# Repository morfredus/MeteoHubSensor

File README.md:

# MeteoHubSensor

> 🇫🇷 Version française : [README.fr.md](README.fr.md)

Standalone outdoor weather probe, linked over **ESP-NOW** to the **MeteoHub** station. Target board: **ESP32-S3 Super Mini** (RGB LED, no screen).

---

## 1. Responsibility

**MeteoHubSensor** has a single responsibility: **measure the outdoor environment and transmit its raw metrics over ESP-NOW**.

This node is **not a new morfSystem component**. No web server, no local history.

### Roles:
- **Super Mini (Outdoor)**: *"I measure, I blink the status, I transmit."*
- **MeteoHub**: *"I receive, validate, store, display and expose."*

---

## 2. ESP-NOW architecture

```
              ┌─────────────────┐
              │  ESP32-S3       │
              │  MeteoHub       │
              └────────┬────────┘
                       │ ESP-NOW
              ┌────────▼────────┐
              │  Super Mini     │
              │  RGB LED        │
              │  AHT20 / BMP280 │
              └────────┬────────┘
                       │
              ┌────────┴────────┐
              ▼                 ▼
         Temperature        Humidity
```

### Changing hub: pairing with a long press on BOOT

The probe talks to **a single** MeteoHub, in unicast. That hub's MAC is stored in
the probe's NVS: there is no need to know it at build time, nor to reflash to
change hub.

1. Leave **only** the MeteoHub to pair powered on within radio range
   (MeteoHub **≥ 1.46.0**).
2. With the probe running, hold **BOOT for about 3 s**, until the LED turns
   **solid blue**, then **release**: pairing starts on release. A press longer
   than 10 s is ignored (button considered stuck). Do not hold BOOT while
   plugging the probe in: that is the ESP32 flashing mode.
3. The probe sweeps channels 1 to 13 asking "who is a hub?". The hub answers with
   its identity and MAC; the probe confirms in unicast and waits for the hub's
   acknowledgement.
4. **3 green flashes**: paired, the new MAC is in NVS and measurements go to this
   hub in unicast. **3 red flashes**: failure, the previous association is **kept
   as it was**.

Rules:

- **Deliberate only.** A hub that is off or out of range never triggers a change
  of receiver: the probe keeps its measurements pending and keeps aiming at its
  hub.
- **A failure erases nothing.** Until a new hub has answered AND acknowledged the
  confirmation, the probe keeps the old MAC (in NVS and in memory).
- **Several hubs in range.** If two different hubs answer during the sweep, the
  probe refuses (red flashes) rather than pick one at random. Once paired, the
  other hubs can be switched back on: the probe finds ITS hub's channel through
  the exact BSSID of its "MH-NOW" access point, no longer through the first
  "MH-NOW" it sees.
- **No duplicate, no gap.** The confirmation carries the last measurement number
  acknowledged by the old hub: the new hub resumes from there and only receives
  the measurements still pending.
- **Stuck button = no effect.** A permanent press (an enclosure pressing the
  button, moisture on GPIO0) is never released: it starts no pairing, and the
  button wake-up is not even armed while GPIO0 stays low. Measurements carry on
  normally.
- Search bounded to **60 s**. A short press is ignored.
- The hub (≥ 1.47.0) **only archives the probe that chose it**: a bench probe
  powered on next to it can no longer mix its readings with the outdoor ones. The
  press wakes the probe from sleep; it then goes back to sleep for the remaining
  time, without shifting the measurement cadence.

Without a stored pairing (new probe, erased flash), the probe **sends nothing**:
`ESPNOW_RECEIVER_MAC` (`include/config.h`) is zero since 0.25.0. It keeps its
measurements pending and no longer scans channels until a long press on BOOT has
paired it. A hard-coded MAC would have targeted one specific hub, and after
swapping hubs (production ↔ test bench) an erased probe would have sent its
readings to the wrong hub.

### Local buffer: no measurement lost, without draining the battery

Each measurement is written to flash **before** it is sent, then kept until the
hub acknowledges it. If the hub is off or out of range, the probe later resends
what is missing, in order, at most 10 measurements per wake-up. Retention: 30
days of pending measurements.

Since 0.24.0 this buffer is a **segmented journal**: one small file per day of
measurements (`/mhs/<seq>.seg`), written by appending only. The acknowledgement
watermark lives in NVS, and a fully acknowledged segment is deleted. The former
buffer, a single 276 KB file, was copied in full by LittleFS at every
measurement: 4.5 s measured, radio on. On the first boot in 0.24.0, the
measurements still pending in the old file are taken over, then it is erased.

---

## 3. Hardware

The pinout lives in `include/board_config.h`, selected by the `SENSOR_BOARD_S3`
define set by the PlatformIO environment.

**ESP32-S3 Super Mini** (env `sonde-supermini`)
- 4 MB flash + 2 MB quad PSRAM (unused), native USB CDC. **No screen** (status on the LED).
- Status = RGB LED on GPIO 48 (blue acquisition, green OK, red error).
- **I2C**: SDA = GP8, SCL = GP9. Battery: Li-ion, 3.3 V regulator module, 100k/100k divider on GP4.
- ESP-NOW capped at **11 dBm** (hardware constraint confirmed by testing: full power = no ACK).
- **Sensors**: DHT22 on GP1 (reference for temperature and humidity, no fallback), BMP280 (pressure only; the AHT20 of the module is no longer read). Anemometer reserve on GP5.
- Details (French): [`docs/cablage.md`](docs/cablage.md).

---

## 4. RGB LED

- **Blue**: boot and acquisition.
- **Green**: delivery confirmed (the hub acknowledged, unicast ACK).
- **Red**: not delivered (no ACK from the hub).
- **Solid blue** (after ~3 s holding BOOT): pairing in progress.
- **3 green / red flashes**: pairing succeeded / failed (association unchanged).

---

## 5. Build and flash

1. Copy `include/secrets_example.h` to `include/secrets.h` **in this project**.

```bash
# ESP32-S3 Super Mini
pio run -e sonde-supermini
pio run -e sonde-supermini -t upload
pio run -e sonde-supermini -t monitor
```

If the serial port does not show up: hold BOOT, tap RESET, release BOOT.

---

## 6. Author & License

Developed by **morfredus** for the **MeteoHub** weather station.
License: **GPL v3**.

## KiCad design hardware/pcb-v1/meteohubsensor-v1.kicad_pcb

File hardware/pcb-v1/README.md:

# Carte v1 de MeteoHubSensor (projet KiCad 10)

Platine dessinée pour remplacer la v1 montée sur platine à bandes (uPesy) : même schéma, mais gravée,
avec l'ESP32-S3 Super Mini sur supports pour pouvoir l'échanger sans dessoudage.

Ouvrir `meteohubsensor-v1.kicad_pro` avec KiCad 10.0.x. Fichiers : schéma, PCB routé (66 x 50 mm, deux
couches, plan de masse GND sur les deux faces), bibliothèque `morfsensor` (symboles et empreintes propres au projet).

## Ce que porte la carte

| Réf. | Rôle | Reliée à |
| :--- | :--- | :--- |
| U1 | ESP32-S3 Super Mini N4R2 sur 2 supports femelles 1x9 | voir ci-dessous |
| U2 | Module abaisseur 3,3 V (Youmi, SOT-223) | VIN = + accu, VOUT = rail 3V3 |
| J1 | Accu (JST-XH 2 broches : + / -) | VBAT, GND |
| J2 | BMP280 (JST-XH 4 broches : 3V3, SCL, SDA, GND) | GP9 (SCL), GP8 (SDA) |
| J3 | DHT22 (JST-XH 3 broches : 3V3, DATA, GND) | GP1 |
| J4 | Anémomètre, futur (3V3, IMPULSION, GND) | GP5 |
| J5 | Pluviomètre, futur (3V3, IMPULSION, GND) | GP7 |
| J6 | Girouette, future (3V3, ADC, GND) | GP2 |
| R1, R2 | Pont 100 kohm / 100 kohm sur le + accu, avant le régulateur | milieu = GP4 |
| C3 | 100 nF sur le noeud du pont (stabilise la lecture ADC) | GP4 / GND |
| C1, C2 | 100 nF céramique + 220 uF électrolytique, collés aux broches 3V3/GND du S3 | rail 3V3 |
| R3 | 10 kohm de rappel du DHT22 (omettre avec un module 3 broches qui l'embarque) | DATA / 3V3 |
| H1 à H4 | Trous de fixation M3 | |

Le régulateur alimente la broche **3V3** du S3 (pas la 5V), comme sur la v1 actuelle. Broches du S3 laissées
libres : TX, RX, GP3, GP6, 5V, GP10 à GP13.

## Masse et modèles 3D

La masse (GND) est un plan de cuivre sur les deux faces : toutes les broches GND des connecteurs et des
composants s'y raccordent par leurs pastilles traversantes, sans piste dédiée. Seules l'alimentation et les signaux
sont tracés. Des pistes GND explicites ont été
essayées puis retirées : elles alourdissaient le dessin sans rien apporter, le plan relie déjà tout.
Les empreintes `ESP32-S3_SuperMini_Socket` et `Regulator_Module_3V3` embarquent un modèle 3D simplifié
(`morfsensor.3dshapes/`) : supports et module avec USB-C et antenne, platine du régulateur avec SOT-223.

## Brochage des connecteurs JST-XH

Broche 1 à gauche (côté de l'ergot carré de l'embase), vue de dessus, détrompeur vers le bas.

| Connecteur | Broche 1 | Broche 2 | Broche 3 | Broche 4 | Référence suivie |
| :--- | :--- | :--- | :--- | :--- | :--- |
| J1 accu | + accu | - accu | | | rouge (+) puis noir (-), usage courant des accus Li-ion |
| J2 BMP280 | 3V3 | SCL | SDA | GND | + puis signaux puis GND, comme les autres ; SCL et SDA se relient sans croisement |
| J3 DHT22 | 3V3 | DATA | GND | | ordre de la fiche technique du DHT22 / AM2302 (VDD, DATA, GND) |
| J4 anémomètre | 3V3 | IMPULSION | GND | | même ordre que J3 |
| J5 pluviomètre | 3V3 | IMPULSION | GND | | même ordre que J3 |
| J6 girouette | 3V3 | ADC | GND | | même ordre que J3 |

Les modules BMP280 courants sont étiquetés dans un autre ordre (VCC, GND, SCL, SDA) : les câbles se sertissent à
l'ordre du connecteur de la carte, pas à celui du module.

## Orientation du module régulateur

Vue de dessus, broches vers le bas (soudées sur la carte), IN à gauche et OUT à droite : sur chaque paire,
VIN (gauche) et VOUT (droite) sont sur la broche du bas, GND sur la broche du haut.

## Repères des broches du S3

Les numéros de pastilles de U1 sont les repères imprimés sur le module, vue de dessus, USB en haut : à
gauche de haut en bas TX, RX, 1, 2, 3, 4, 5, 6, 7 ; à droite de haut en bas 5V, GND, 3V3, 13, 12, 11, 10, 9, 8.
Pastille 8 = GPIO8 = SDA, pastille 9 = GPIO9 = SCL, et ainsi de suite : aucune table de correspondance à tenir.
J6 (girouette) ne porte que le signal brut sur GP2 : le pont diviseur propre à la girouette reste à définir
avec le firmware.

## Antenne

Le S3 est implanté **USB vers l'intérieur** : l'antenne céramique se retrouve au **bord bas** de la carte.
Une zone d'exclusion (cuivre, pistes, vias, plan de masse, sur les deux faces) couvre l'espace sous l'antenne
et jusqu'au bord. Aucune piste n'approche l'antenne : les signaux des deux rangées partent vers l'extérieur.

Limite connue : l'USB du module est tourné vers l'intérieur de la carte. Pour flasher, enlever le module de
ses supports (c'est l'intérêt de la prise).

## Cotes relevées sur les modules

- **ESP32-S3 Super Mini** : 15,9 mm hors tout entre les deux rangées de broches, soit 15,24 mm entre axes (broche de
  0,64 mm), pas de 2,54 mm comme sur une platine d'essai. Empreinte `ESP32-S3_SuperMini_Socket`.
- **Module régulateur** : circuit de 25,6 x 11,3 mm. Broches standard (0,64 mm) sur la grille de 2,54 mm, comme les
  deux modules qui entrent dans une platine d'essai : deux paires espacées de 22,86 mm entre axes (9 pas) dans la
  longueur, pas de 2,54 mm dans chaque paire (3 mm hors tout dans la largeur). Empreinte `Regulator_Module_3V3`.
  La position des paires dans la largeur du circuit est supposée centrée : elle ne change que le contour dessiné,
  pas le perçage.

## À vérifier avant fabrication

1. **Module régulateur** : vérifier que son orientation réelle (IN à gauche, VIN sur la broche du bas) correspond à
   l'empreinte, en le posant sur la carte imprimée ou sur un gabarit.
2. **Connecteurs** : les câbles existants ne suivent pas forcément cet ordre ; les recréer au brochage du tableau.

Rappel du point de vigilance de `docs/cablage.md` : la plage d'entrée annoncée du module (4,5 à 7 V) est
au-dessus de celle d'un accu Li-ion. À mesurer sur banc avant de figer la carte.

## Contrôles passés (KiCad 10.0.7, `kicad-cli`)

- ERC : 0 violation.
- DRC avec parité schéma/PCB : 0 erreur, 0 piste non connectée. Restent des avertissements de sérigraphie
  (textes proches des contours de connecteurs).

Les fichiers ont été générés par script puis vérifiés par ces commandes ; les ouvrir une fois dans KiCad et
lancer `Fichier > Enregistrer` les remet au format exact de l'éditeur.

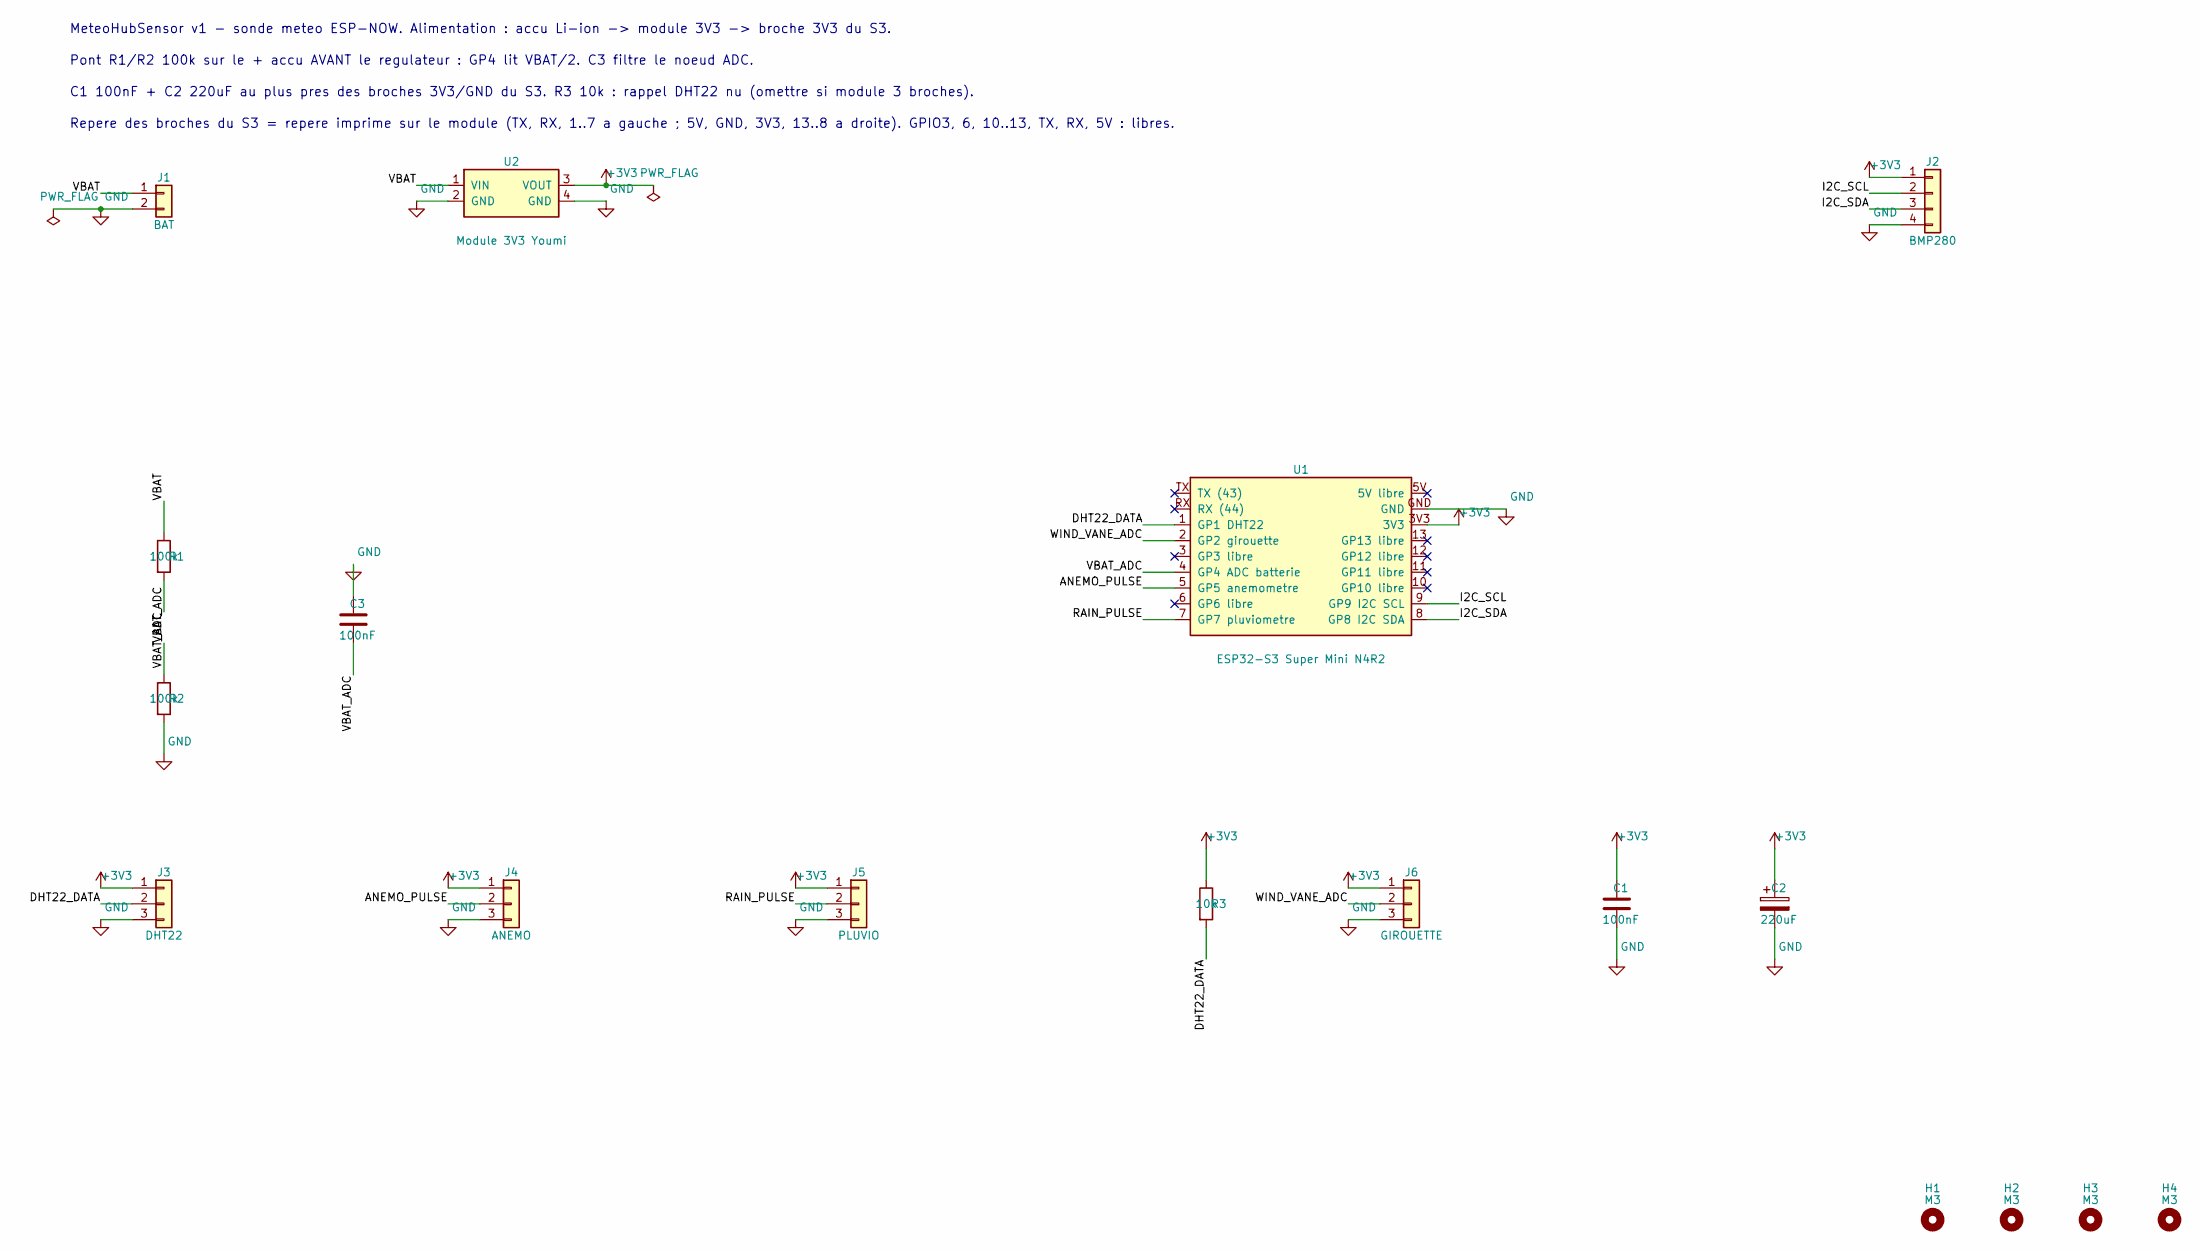
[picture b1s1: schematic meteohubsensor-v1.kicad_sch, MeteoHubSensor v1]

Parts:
C1, C3: 100nF; C_Disc_D3.0mm_W2.0mm_P2.50mm
C2: 220uF; CP_Radial_D6.3mm_P2.50mm
H1, H2, H3, H4: M3; MountingHole_3.2mm_M3
J1: BAT; JST_XH_B2B-XH-A_1x02_P2.50mm_Vertical
J2: BMP280; JST_XH_B4B-XH-A_1x04_P2.50mm_Vertical
J3: DHT22; JST_XH_B3B-XH-A_1x03_P2.50mm_Vertical
J4: ANEMO; JST_XH_B3B-XH-A_1x03_P2.50mm_Vertical
J5: PLUVIO; JST_XH_B3B-XH-A_1x03_P2.50mm_Vertical
J6: GIROUETTE; JST_XH_B3B-XH-A_1x03_P2.50mm_Vertical
R1, R2: 100k; R_Axial_DIN0207_L6.3mm_D2.5mm_P2.54mm_Vertical
R3: 10k; R_Axial_DIN0207_L6.3mm_D2.5mm_P2.54mm_Vertical
U1: ESP32-S3 Super Mini N4R2; ESP32-S3_SuperMini_Socket
U2: Module 3V3 Youmi; Regulator_Module_3V3

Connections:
+3V3: C1.1, C2.1, J2.1, J3.1, J4.1, J5.1, J6.1, R3.1, U1.3V3, U2.3 (VOUT)
/ANEMO_PULSE: J4.2, U1.5 (GP5 anemometre)
/DHT22_DATA: J3.2, R3.2, U1.1 (GP1 DHT22)
/I2C_SCL: J2.2, U1.9 (GP9 I2C SCL)
/I2C_SDA: J2.3, U1.8 (GP8 I2C SDA)
/RAIN_PULSE: J5.2, U1.7 (GP7 pluviometre)
/VBAT: J1.1, R1.1, U2.1 (VIN)
/VBAT_ADC: C3.2, R1.2, R2.1, U1.4 (GP4 ADC batterie)
/WIND_VANE_ADC: J6.2, U1.2 (GP2 girouette)
GND: C1.2, C2.2, C3.1, J1.2, J2.4, J3.3, J4.3, J5.3, J6.3, R2.2, U1.GND, U2.2 (GND), U2.4 (GND)

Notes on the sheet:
MeteoHubSensor v1 - sonde meteo ESP-NOW. Alimentation : accu Li-ion -> module 3V3 -> broche 3V3 du S3.
Pont R1/R2 100k sur le + accu AVANT le regulateur : GP4 lit VBAT/2. C3 filtre le noeud ADC.
C1 100nF + C2 220uF au plus pres des broches 3V3/GND du S3. R3 10k : rappel DHT22 nu (omettre si module 3 broches).
Repere des broches du S3 = repere imprime sur le module (TX, RX, 1..7 a gauche ; 5V, GND, 3V3, 13..8 a droite). GPIO3, 6, 10..13, TX, RX, 5V : libres.

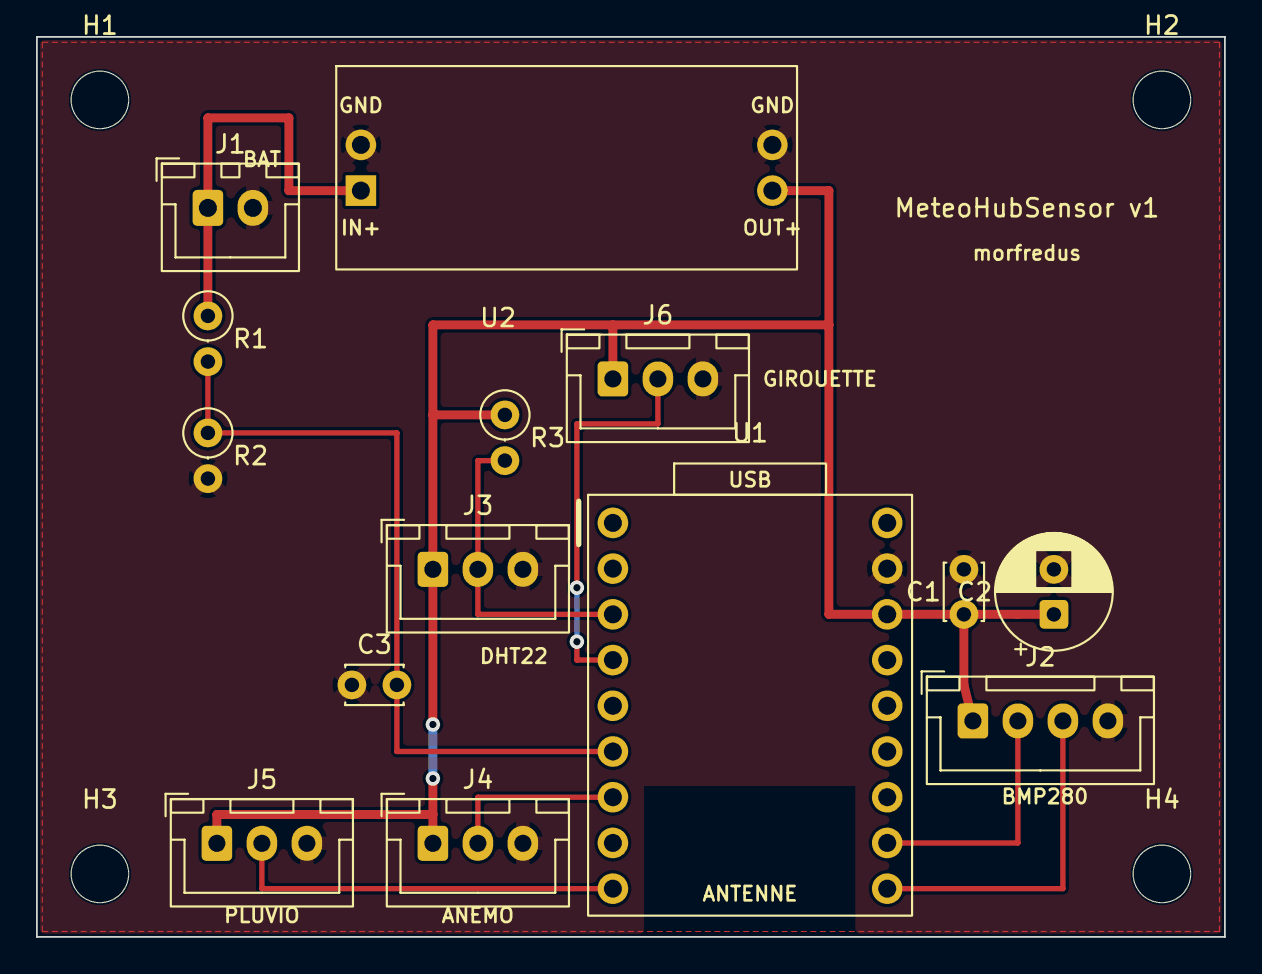
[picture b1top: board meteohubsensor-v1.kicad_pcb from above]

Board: 2 copper layers, 66.0 x 50.0 mm, 18 parts (0 on the bottom side), 10 nets.

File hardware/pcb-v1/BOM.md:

# Liste des composants - carte v1 de MeteoHubSensor

Liste tirée du schéma (`meteohubsensor-v1.kicad_sch`). Toutes les pièces de la carte sont traversantes : aucune
soudure CMS, **52 pastilles à souder** au total. Aucune référence de fournisseur (LCSC, Mouser...) n'est donnée :
elles n'ont pas été vérifiées.

## 1. Soudé sur la carte

### Résistances (3)

| Réf. | Qté | Valeur | Détail | Rôle |
| :--- | :-: | :--- | :--- | :--- |
| R1, R2 | 2 | 100 kohm | Axiale 1/4 W, tolérance **1 %** conseillée, boîtier DIN0207 | Pont de mesure de l'accu (GP4) |
| R3 | 1 | 10 kohm | Axiale 1/4 W, boîtier DIN0207 | Rappel du DHT22 (omettre avec un module 3 broches qui l'embarque) |

### Condensateurs (3)

| Réf. | Qté | Valeur | Détail | Rôle |
| :--- | :-: | :--- | :--- | :--- |
| C1 | 1 | 100 nF | Céramique disque, 50 V, pas 2,5 mm | Découplage près des broches 3V3/GND du S3 |
| C3 | 1 | 100 nF | Céramique disque, 50 V, pas 2,5 mm | Filtre du noeud ADC (GP4) |
| C2 | 1 | 220 uF | Électrolytique radial, **10 V ou plus**, diamètre 6,3 mm, pas 2,5 mm | Réserve de courant pour les pointes d'émission |

### Embases JST-XH (6 embases, 18 broches), pas 2,50 mm, verticales

| Réf. | Nom | Broches | Référence JST | Brochage (1 à n) |
| :--- | :--- | :-: | :--- | :--- |
| J1 | BAT | 2 | B2B-XH-A | + accu, - accu |
| J2 | BMP280 | 4 | B4B-XH-A | 3V3, SCL, SDA, GND |
| J3 | DHT22 | 3 | B3B-XH-A | 3V3, DATA, GND |
| J4 | ANEMO | 3 | B3B-XH-A | 3V3, impulsion, GND |
| J5 | PLUVIO | 3 | B3B-XH-A | 3V3, impulsion, GND |
| J6 | GIROUETTE | 3 | B3B-XH-A | 3V3, ADC, GND |

Récapitulatif : 1 x 2 broches, 4 x 3 broches (12 broches), 1 x 4 broches, soit 2 + 12 + 4 = 18 broches.

### Supports et module

| Réf. | Qté | Pièce | Détail |
| :--- | :-: | :--- | :--- |
| U1 | 2 | Barrette femelle 1x9, pas 2,54 mm | Une par rangée du S3 (18 broches au total), entraxe des rangées 15,24 mm |
| U2 | 1 | Module abaisseur 3,3 V (Youmi, SOT-223) | 4 broches mâles soudées : deux paires espacées de 22,86 mm, circuit 25,6 x 11,3 mm |

Trous de fixation H1 à H4 : 4 trous M3 (3,2 mm), aucune pièce sur la carte.

## 2. À fournir, non soudé sur la carte

| Qté | Pièce | Remarque |
| :-: | :--- | :--- |
| 1 | ESP32-S3 Super Mini N4R2 | Se pose sur les supports U1, USB-C vers l'intérieur de la carte |
| 1 | Module BMP280 (avec ou sans AHT20) | Seule la pression est lue |
| 1 | DHT22 (ou module 3 broches) | Température et humidité de référence |
| 1 | Accu Li-ion 3,7 V | 3000 mAh en place ; chargé hors de la sonde, sans protection sur cette carte |
| 1 | Anémomètre, 1 pluviomètre, 1 girouette | Futurs ; seuls les connecteurs J4, J5, J6 sont prévus |
| 1 | Boîtier femelle JST-XHP 2 broches | Pour J1 |
| 4 | Boîtiers femelles JST-XHP 3 broches | Pour J3, J4, J5, J6 |
| 1 | Boîtier femelle JST-XHP 4 broches | Pour J2 |
| 18 | Cosses à sertir JST-XH (SXH) | 2 + 12 + 4, prévoir quelques cosses de plus pour les ratés de sertissage |
| - | Fil souple 22 à 26 AWG | Pour les câbles des capteurs et de l'accu |
| 4 | Vis M3 et entretoises | Pour la fixation, si le boîtier en demande |

## 3. Totaux

| Famille | Pièces | Pastilles à souder |
| :--- | :-: | :-: |
| Résistances | 3 | 6 |
| Condensateurs | 3 | 6 |
| Embases JST-XH | 6 | 18 |
| Barrettes femelles 1x9 | 2 | 18 |
| Module régulateur | 1 | 4 |
| **Total** | **15** | **52** |

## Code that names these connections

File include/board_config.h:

#pragma once
#include <Arduino.h>

// ============================================================================
// Brochage MeteoHubSensor - ESP32-S3 Super Mini
// ============================================================================
// Cible unique (env sonde-supermini, define SENSOR_BOARD_S3). Le reste du firmware ne
// connait que les alias PIN_* et le drapeau SENSOR_NEEDS_TX_LIMIT : ajouter une
// autre carte se ferait ici, sans toucher aux modules. (La cible C3 HW-675 a ete
// retiree, et avec elle le module d'ecran OLED qui ne servait qu'a elle.)
// ============================================================================

// ---------------------------------------------------------------------------
// ESP32-S3 Super Mini (LED RGB seule, sans ecran)
// ---------------------------------------------------------------------------
// USB natif : GPIO 19/20. BOOT : GPIO 0 (non sorti). Straps : 45/46.
// LED RGB onboard : GPIO 48 (GPIO 46 = input-only, ignore malgre le pinout).
constexpr char BOARD_NAME[] = "ESP32-S3 Super Mini";

// --- Module BMP280 (0x77) + AHT20 (0x38) : seule la pression du BMP280 est utilisee ---
// Cablage : fil SDA du module -> GP8, fil SCL du module -> GP9, 3V3, GND.
constexpr uint8_t PIN_SENSOR_SDA = 8;
constexpr uint8_t PIN_SENSOR_SCL = 9;
constexpr int8_t PIN_SENSOR_POWER = -1; // -1 = alim 3V3 permanente

// LED RGB onboard.
constexpr int8_t PIN_LED_RGB = 48;
constexpr uint8_t NUM_PIXELS = 1;

// Bouton BOOT.
constexpr uint8_t PIN_BOOT_BUTTON = 0;

// Alimentation : module regulateur Youmi 3,3 V (entree annoncee 4,5-7 V) + accu Li-ion
// 3,7 V (3000 mAh depuis le 2026-10-03), charge dans un chargeur de bureau (pas de
// charge USB) ; deux accus a permuter. Il a remplace le module Breadvolt (boost, protection decharge
// 2,4 V / charge 4,28 V) qui decrochait en deep sleep. Le 3,3 V regule est CONSTANT :
// le mesurer ne dirait rien de l'accu. On tape donc la CELLULE, AVANT le
// regulateur, au + de l'accu (multimetre ~4,0 V en charge).
//
// Cablage batterie (2026-09-15) : + accu --[R1 100k]--(GP4)--[R2 100k]-- GND.
// GP4 lit le point milieu = tension accu / 2 (~2,0 V pour 4,0 V), sous la limite
// ADC du S3 : indispensable, l'accu monte a 4,28 V en pleine charge et ne doit
// JAMAIS arriver brut sur la pin. Le firmware remultiplie par le ratio du pont
// (BATTERY_DIVIDER_RATIO = 2,0 dans config.h). Le pont draine en continu
// ~4,0 V / 200 k = 20 uA, negligeable devant les reveils TX. La plage Li-ion
// 2,6-4,2 ci-dessous convertit en pourcentage.
constexpr int8_t PIN_BATTERY_ADC = 4;
// Bornes de la plage de PLAUSIBILITE de la lecture (garde de power_manager.cpp, +/- 0,5 V) :
// elles ne servent plus au pourcentage, calcule par la courbe Li-ion de battery_curve.h.
// 2,6 V = 0,2 V au-dessus de la coupure 2,4 V de l'ancien Breadvolt : une pile presque
// vide doit encore etre signalee, pas rejetee. Sous ~3,0 V la courbe Li-ion s'effondre.
constexpr float BATTERY_VOLTAGE_MIN = 2.6f;
constexpr float BATTERY_VOLTAGE_MAX = 4.2f; // Li-ion pleine charge
// Facteur de calibration fin propre a CE S3 + CE pont (voir config.h).
// Accu Li-ion 3,7 V 3000 mAh, 2026-10-03. Releves multimetre / sonde (facteur 1,0515 pose) :
//   3,927 V / 3,98 V rapportes  -> facteur reel 1,0377
//   4,074 V / 4,14 V rapportes  -> facteur reel 1,0347      moyenne retenue : 1,036
// Le premier releve (3,859 V pour 3,67 V avec l'ancien firmware, soit 1,0515) s'ecarte de
// 1,5 % : mesure non simultanee, accu fraichement sorti du chargeur. Residu avec 1,036 :
// -0,2 % et +0,1 % sur les deux points retenus. L'ecart tient surtout a l'impedance du pont
// 100k/100k (50 kohm vue par l'ADC) ; il est proportionnel a la tension. A reverifier
// a pleine charge stable (~4,2 V) et a mi-charge ; un condensateur 100 nF GP4-GND
// rendrait la lecture plus juste et plus stable. Reposer : facteur = actuel x Vmultimetre / Vlu.
constexpr float BATTERY_VREF_CALIBRATION = 1.036f;

// --- DHT22 : reference temperature ET humidite (calibre en sel sature a 75 %, voir docs/notes.md) ---
// Fil DATA -> GP1, 3V3, GND (module 3 broches : resistance de rappel deja presente ; DHT22 nu : 10 k vers 3V3).
constexpr uint8_t PIN_DHT22 = 1;
// Correctifs de calibration (ajoutes a la lecture). Sel sature NaCl : 75,0 a 75,1 % pendant 2 h -> 0.
constexpr float DHT22_HUM_OFFSET = 0.0f;
constexpr float DHT22_TEMP_OFFSET = 0.0f;

// --- Reserves meteo ---
constexpr uint8_t PIN_ANEMOMETER_PULSE = 5; // deplace de GP1 (0.30.0) : GP1 sert au DHT22
constexpr uint8_t PIN_WIND_VANE_ADC = 2;
constexpr uint8_t PIN_RAIN_GAUGE_PULSE = 7;
constexpr uint8_t PIN_AUX_ADC = 10;
constexpr uint8_t PIN_FREE_GP6 = 6;

// Pas d'ecran : le statut passe par la LED RGB seule. Un ecran eventuellement
// cable mais jamais initialise reste dans son etat reset basse conso.

// Plafond TX ESP-NOW sur le S3 (2026-09-14). Preuve terrain (logs USB, firmware
// 0.13.0 unicast) : a pleine puissance, le S3 emet mais le hub ne renvoie PAS
// d'ACK (NACK a tous les essais). L'antenne PCB du S3 Super Mini est mal adaptee :
// trop de puissance = signal trop degrade pour etre acquitte. On plafonne donc,
// valeur reglee dans config.h (SENSOR_TX_POWER_LEVEL), a remonter progressivement
// (menu config.h) pour retrouver le maximum de portee qui reste stable.
#define SENSOR_NEEDS_TX_LIMIT 1

// Alias I2C (meme bus, memes GPIO).
constexpr uint8_t PIN_I2C_SDA = PIN_SENSOR_SDA;
constexpr uint8_t PIN_I2C_SCL = PIN_SENSOR_SCL;
